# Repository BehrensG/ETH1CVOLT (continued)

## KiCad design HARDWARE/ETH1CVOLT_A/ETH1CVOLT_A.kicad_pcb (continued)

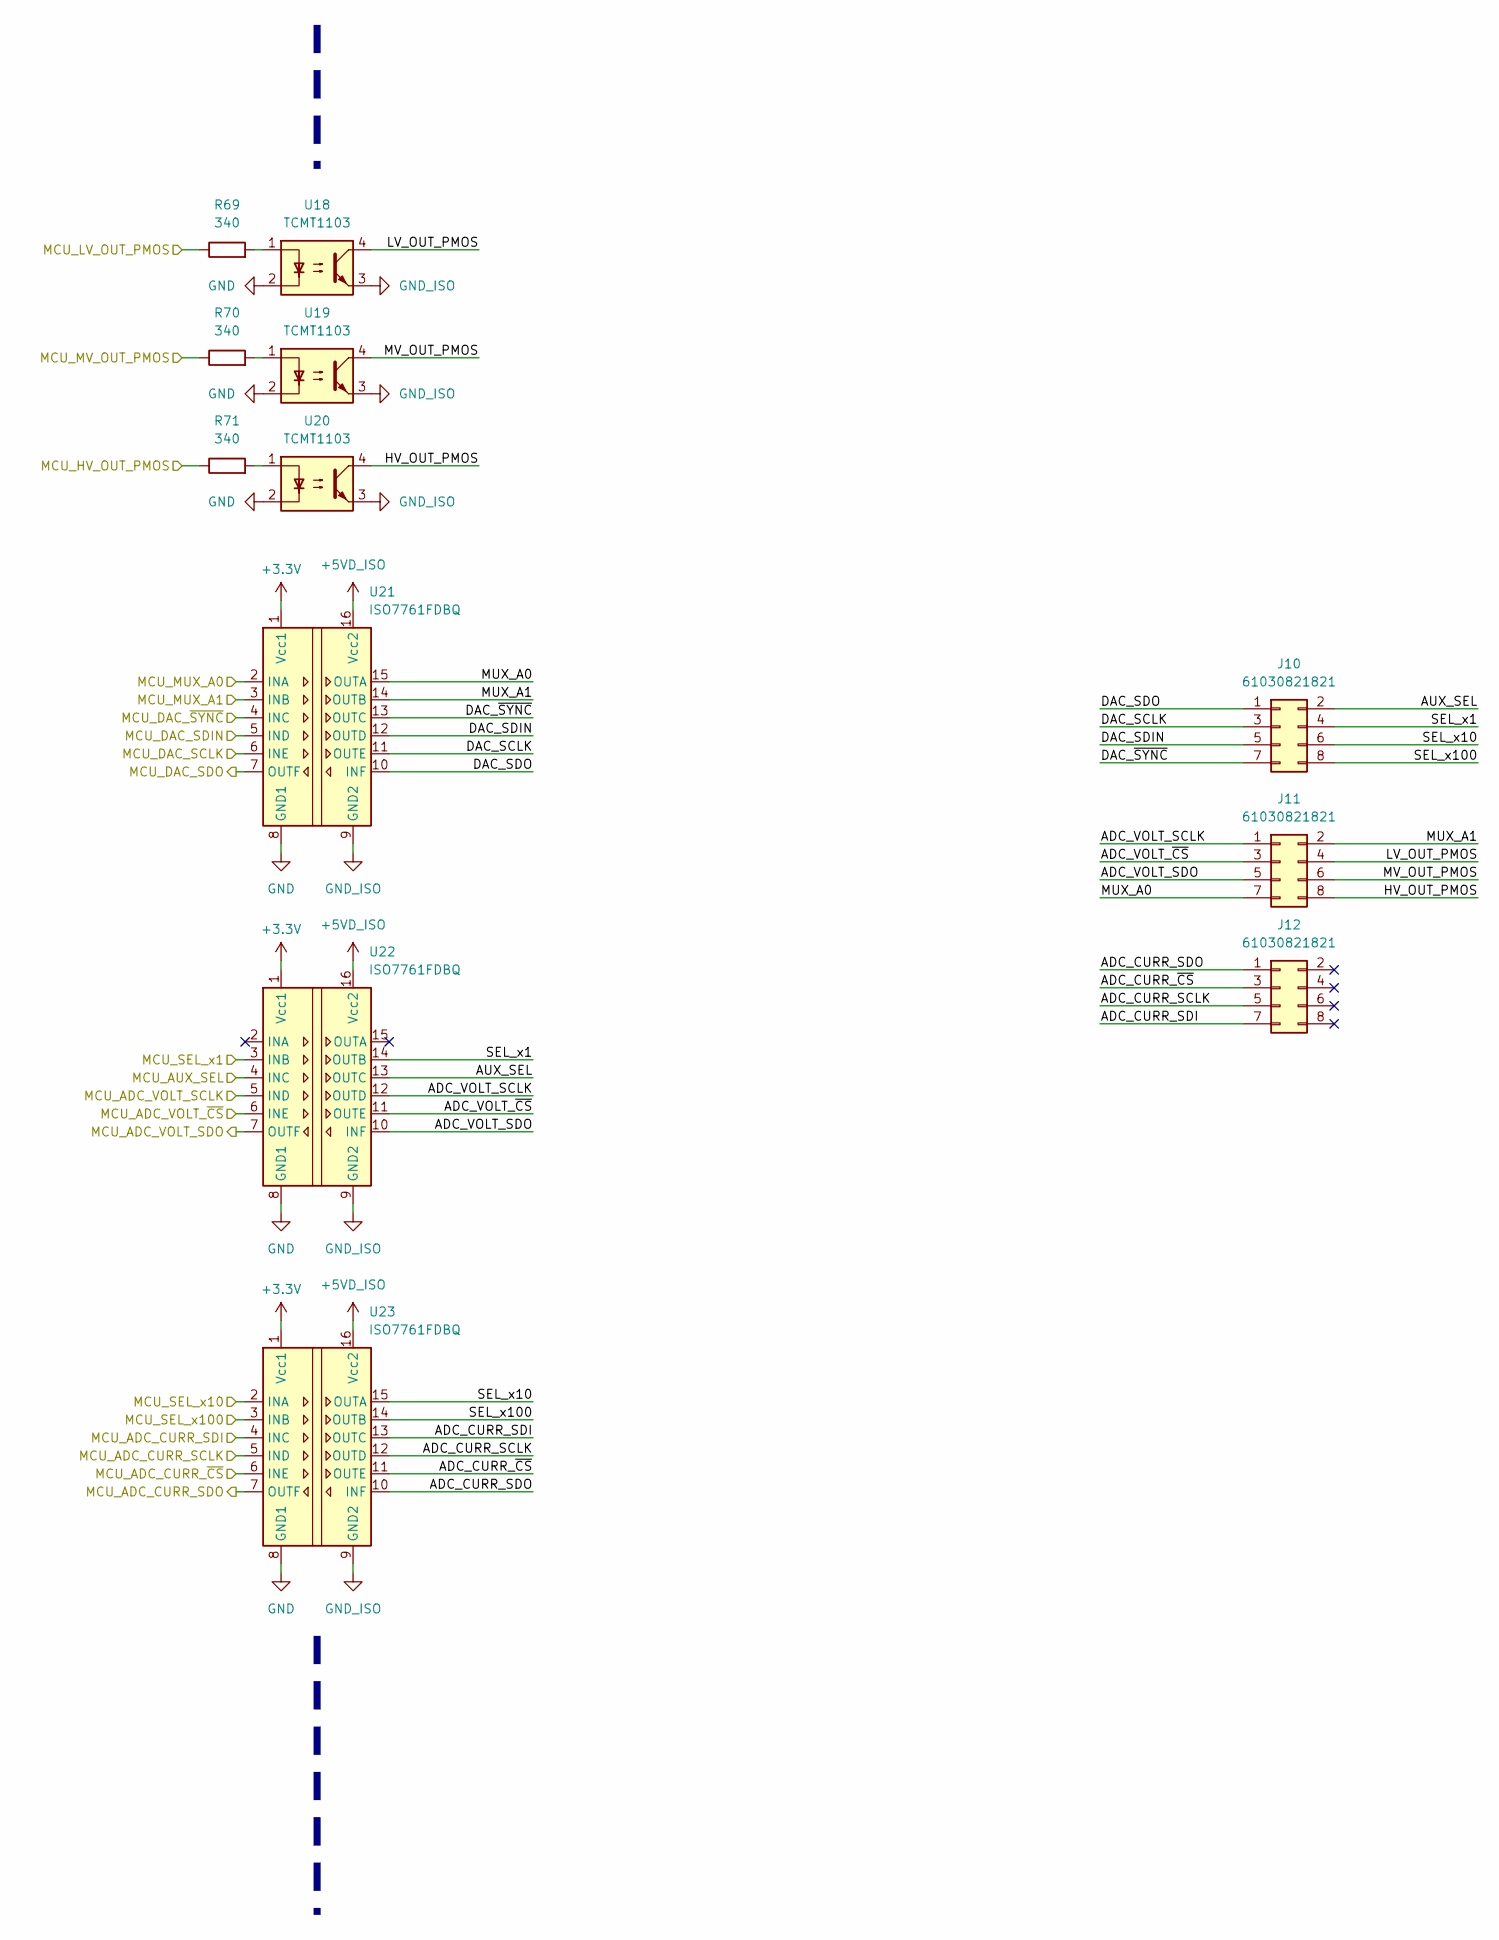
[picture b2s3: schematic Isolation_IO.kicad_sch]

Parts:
J10, J11, J12: 61030821821; PinSocket_2x04_P2.54mm_Vertical_SMD
R69, R70, R71: 340; R_0603_1608Metric_Pad0.98x0.95mm_HandSolder
U18, U19, U20: TCMT1103; SOP-4_4.4x2.6mm_P1.27mm
U21, U22, U23: ISO7761FDBQ; SSOP-16_3.9x4.9mm_P0.635mm

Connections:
+3.3V: U21.1 (Vcc1), U22.1 (Vcc1), U23.1 (Vcc1); also elsewhere on the board
+5VD_ISO: U21.16 (Vcc2), U22.16 (Vcc2), U23.16 (Vcc2); also elsewhere on the board
/Block Diagram/Isolation IO/ADC_CURR_SCLK: J12.5, U23.12 (OUTD)
/Block Diagram/Isolation IO/ADC_CURR_SDI: J12.7, U23.13 (OUTC)
/Block Diagram/Isolation IO/ADC_CURR_SDO: J12.1, U23.10 (INF)
/Block Diagram/Isolation IO/ADC_CURR_~CS: J12.3, U23.11 (OUTE)
/Block Diagram/Isolation IO/ADC_VOLT_SCLK: J11.1, U22.12 (OUTD)
/Block Diagram/Isolation IO/ADC_VOLT_SDO: J11.5, U22.10 (INF)
/Block Diagram/Isolation IO/ADC_VOLT_~CS: J11.3, U22.11 (OUTE)
/Block Diagram/Isolation IO/AUX_SEL: J10.2, U22.13 (OUTC)
/Block Diagram/Isolation IO/DAC_SCLK: J10.3, U21.11 (OUTE)
/Block Diagram/Isolation IO/DAC_SDIN: J10.5, U21.12 (OUTD)
/Block Diagram/Isolation IO/DAC_SDO: J10.1, U21.10 (INF)
/Block Diagram/Isolation IO/DAC_~SYNC: J10.7, U21.13 (OUTC)
/Block Diagram/Isolation IO/HV_OUT_PMOS: J11.8, U20.4
/Block Diagram/Isolation IO/LV_OUT_PMOS: J11.4, U18.4
/Block Diagram/Isolation IO/MCU_ADC_CURR_SCLK: U23.5 (IND); also elsewhere on the board
/Block Diagram/Isolation IO/MCU_ADC_CURR_SDI: U23.4 (INC); also elsewhere on the board
/Block Diagram/Isolation IO/MCU_ADC_CURR_SDO: U23.7 (OUTF); also elsewhere on the board
/Block Diagram/Isolation IO/MCU_ADC_CURR_~CS: U23.6 (INE); also elsewhere on the board
/Block Diagram/Isolation IO/MCU_ADC_VOLT_SCLK: U22.5 (IND); also elsewhere on the board
/Block Diagram/Isolation IO/MCU_ADC_VOLT_SDO: U22.7 (OUTF); also elsewhere on the board
/Block Diagram/Isolation IO/MCU_ADC_VOLT_~CS: U22.6 (INE); also elsewhere on the board
/Block Diagram/Isolation IO/MCU_AUX_SEL: U22.4 (INC); also elsewhere on the board
/Block Diagram/Isolation IO/MCU_DAC_SCLK: U21.6 (INE); also elsewhere on the board
/Block Diagram/Isolation IO/MCU_DAC_SDIN: U21.5 (IND); also elsewhere on the board
/Block Diagram/Isolation IO/MCU_DAC_SDO: U21.7 (OUTF); also elsewhere on the board
/Block Diagram/Isolation IO/MCU_DAC_~SYNC: U21.4 (INC); also elsewhere on the board
/Block Diagram/Isolation IO/MCU_HV_OUT_PMOS: R71.1; also elsewhere on the board
/Block Diagram/Isolation IO/MCU_LV_OUT_PMOS: R69.1; also elsewhere on the board
/Block Diagram/Isolation IO/MCU_MUX_A0: U21.2 (INA); also elsewhere on the board
/Block Diagram/Isolation IO/MCU_MUX_A1: U21.3 (INB); also elsewhere on the board
/Block Diagram/Isolation IO/MCU_MV_OUT_PMOS: R70.1; also elsewhere on the board
/Block Diagram/Isolation IO/MCU_SEL_x1: U22.3 (INB); also elsewhere on the board
/Block Diagram/Isolation IO/MCU_SEL_x10: U23.2 (INA); also elsewhere on the board
/Block Diagram/Isolation IO/MCU_SEL_x100: U23.3 (INB); also elsewhere on the board
/Block Diagram/Isolation IO/MUX_A0: J11.7, U21.15 (OUTA)
/Block Diagram/Isolation IO/MUX_A1: J11.2, U21.14 (OUTB)
/Block Diagram/Isolation IO/MV_OUT_PMOS: J11.6, U19.4
/Block Diagram/Isolation IO/SEL_x1: J10.4, U22.14 (OUTB)
/Block Diagram/Isolation IO/SEL_x10: J10.6, U23.15 (OUTA)
/Block Diagram/Isolation IO/SEL_x100: J10.8, U23.14 (OUTB)
GND: U18.2, U19.2, U20.2, U21.8 (GND1), U22.8 (GND1), U23.8 (GND1); also elsewhere on the board
GND_ISO: U18.3, U19.3, U20.3, U21.9 (GND2), U22.9 (GND2), U23.9 (GND2); also elsewhere on the board
unnamed: R69.2, U18.1
unnamed: R70.2, U19.1
unnamed: R71.2, U20.1

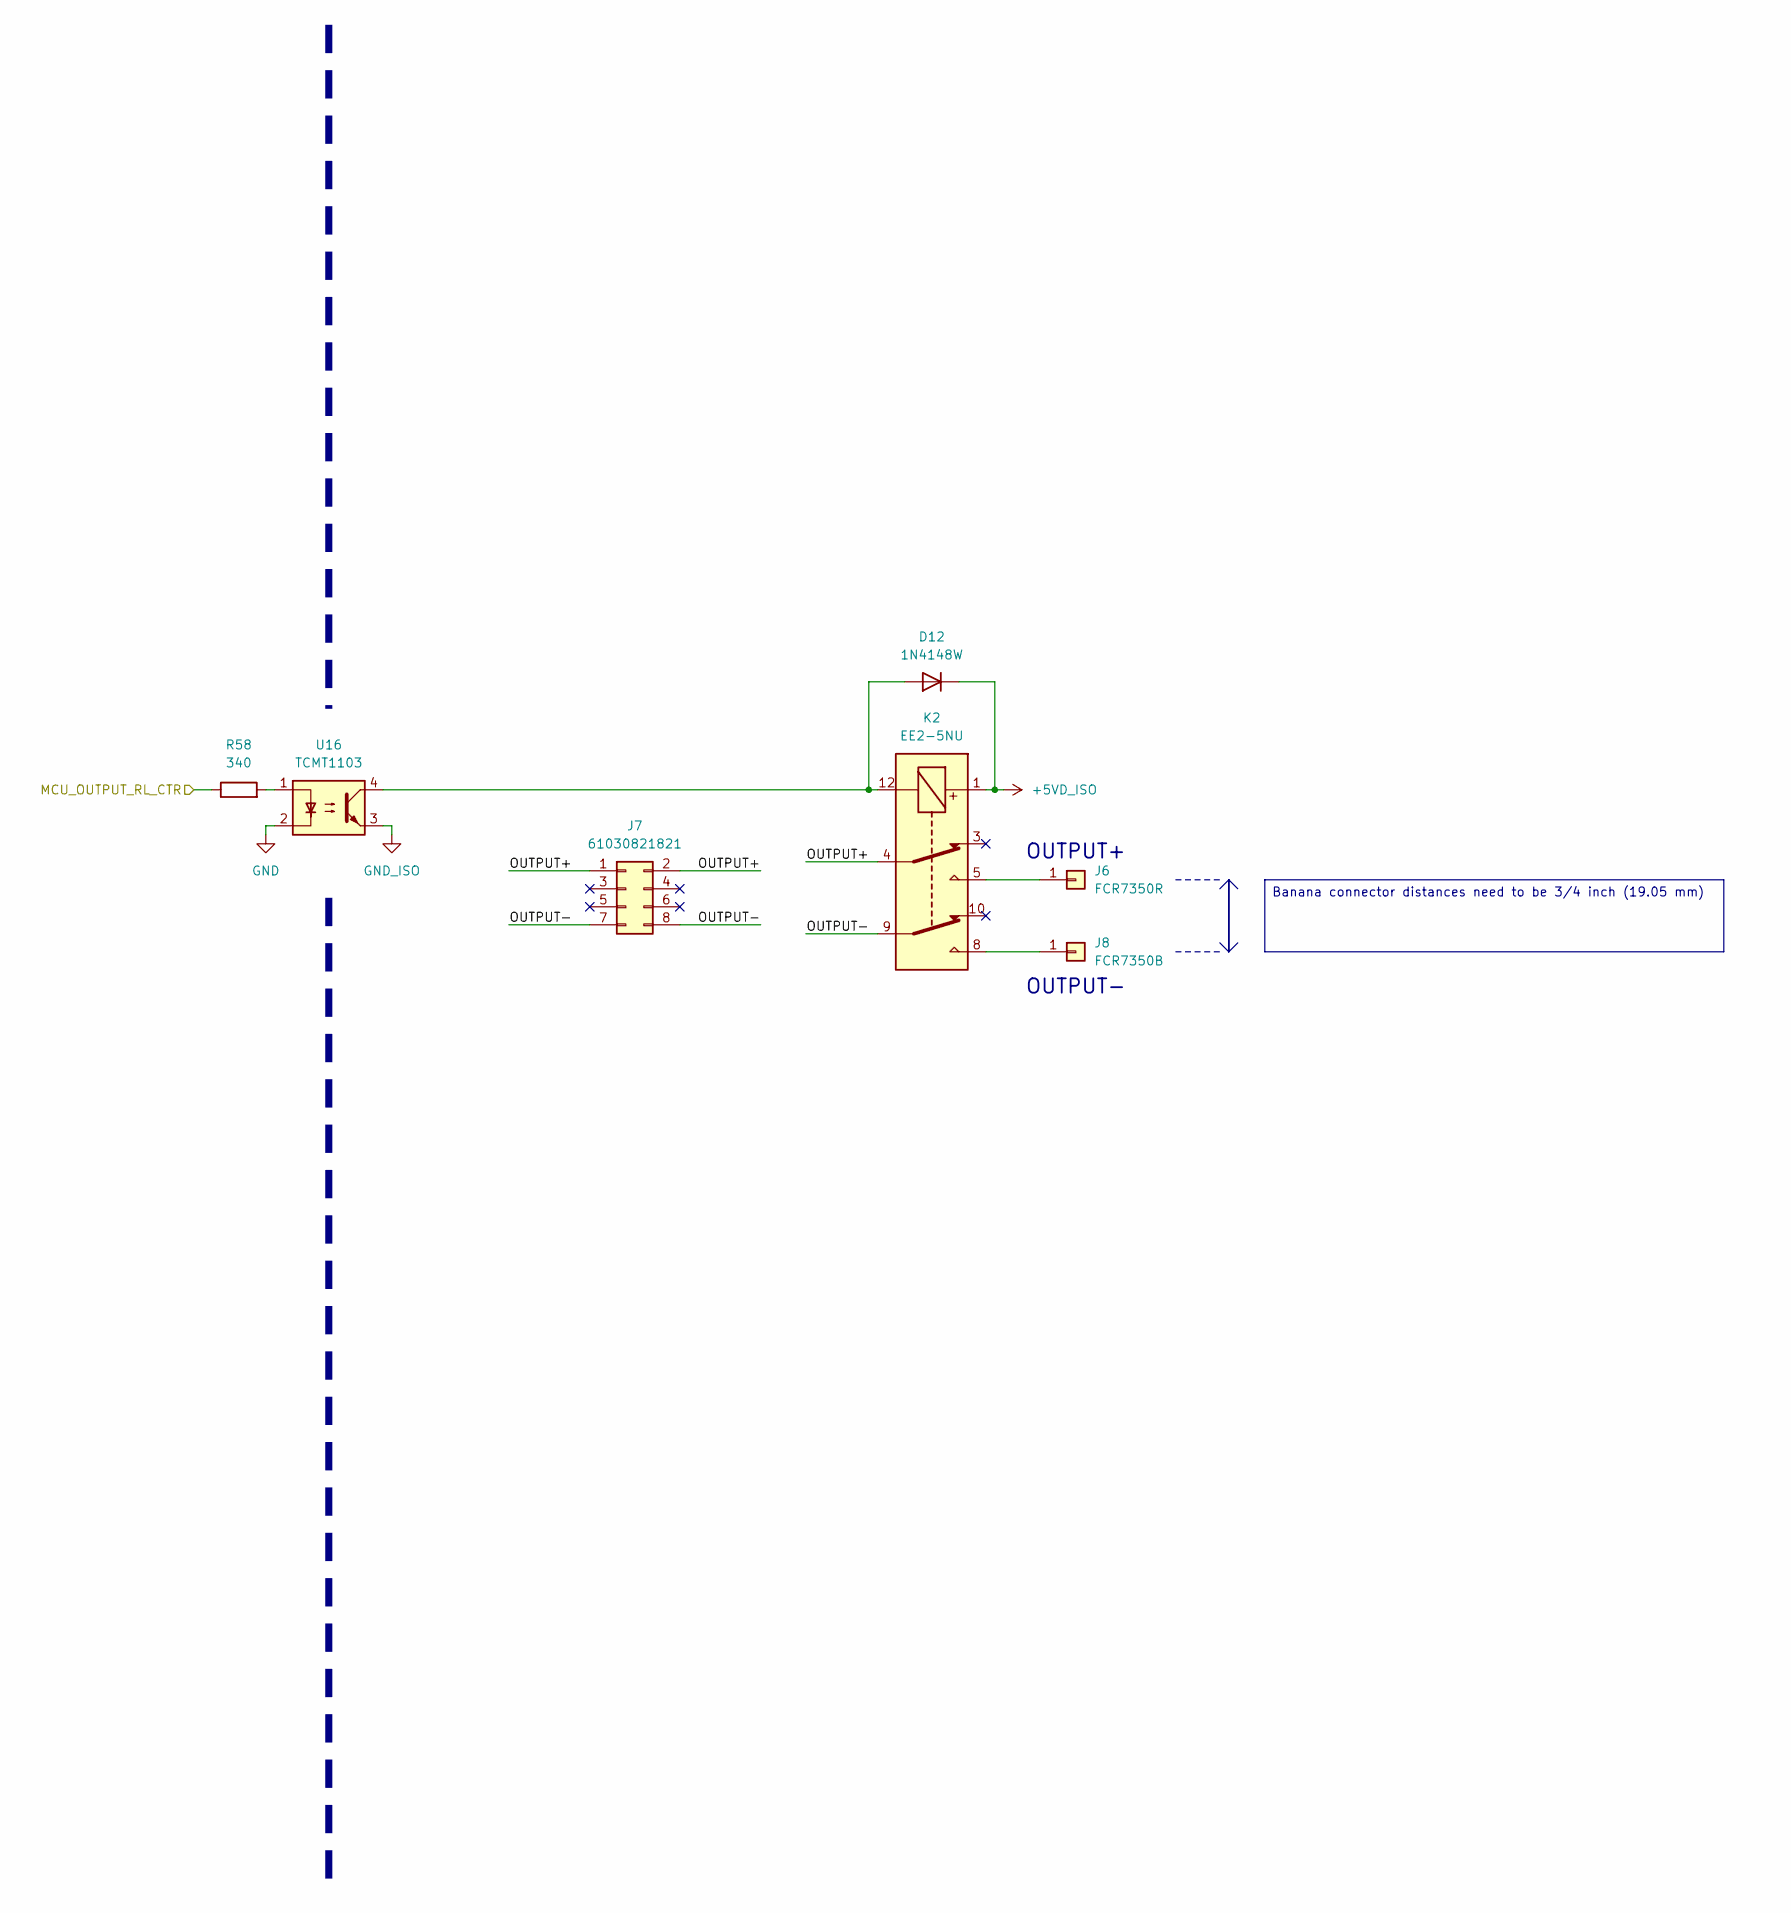
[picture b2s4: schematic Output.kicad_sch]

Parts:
D12: 1N4148W; D_SOD-123
J6: FCR7350R; S16N-PC
J7: 61030821821; PinSocket_2x04_P2.54mm_Vertical_SMD
J8: FCR7350B; S16N-PC
K2: EE2-5NU; Relay_DPDT_Kemet_EE2_NU
R58: 340; R_0603_1608Metric_Pad0.98x0.95mm_HandSolder
U16: TCMT1103; SOP-4_4.4x2.6mm_P1.27mm

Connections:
+5VD_ISO: D12.1 (K), K2.1; also elsewhere on the board
/Block Diagram/MCU/MCU_OUTPUT_RL_CTR: R58.1; also elsewhere on the board
/Block Diagram/Output/OUTPUT+: J7.1, J7.2, K2.4
/Block Diagram/Output/OUTPUT-: J7.7, J7.8, K2.9
GND: U16.2; also elsewhere on the board
GND_ISO: U16.3; also elsewhere on the board
unnamed: D12.2 (A), K2.12, U16.4
unnamed: J6.1 (Pin_1_1), K2.5
unnamed: J8.1 (Pin_1_1), K2.8
unnamed: R58.2, U16.1

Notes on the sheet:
OUTPUT+
OUTPUT-
Banana connector distances need to be 3/4 inch (19.05 mm)

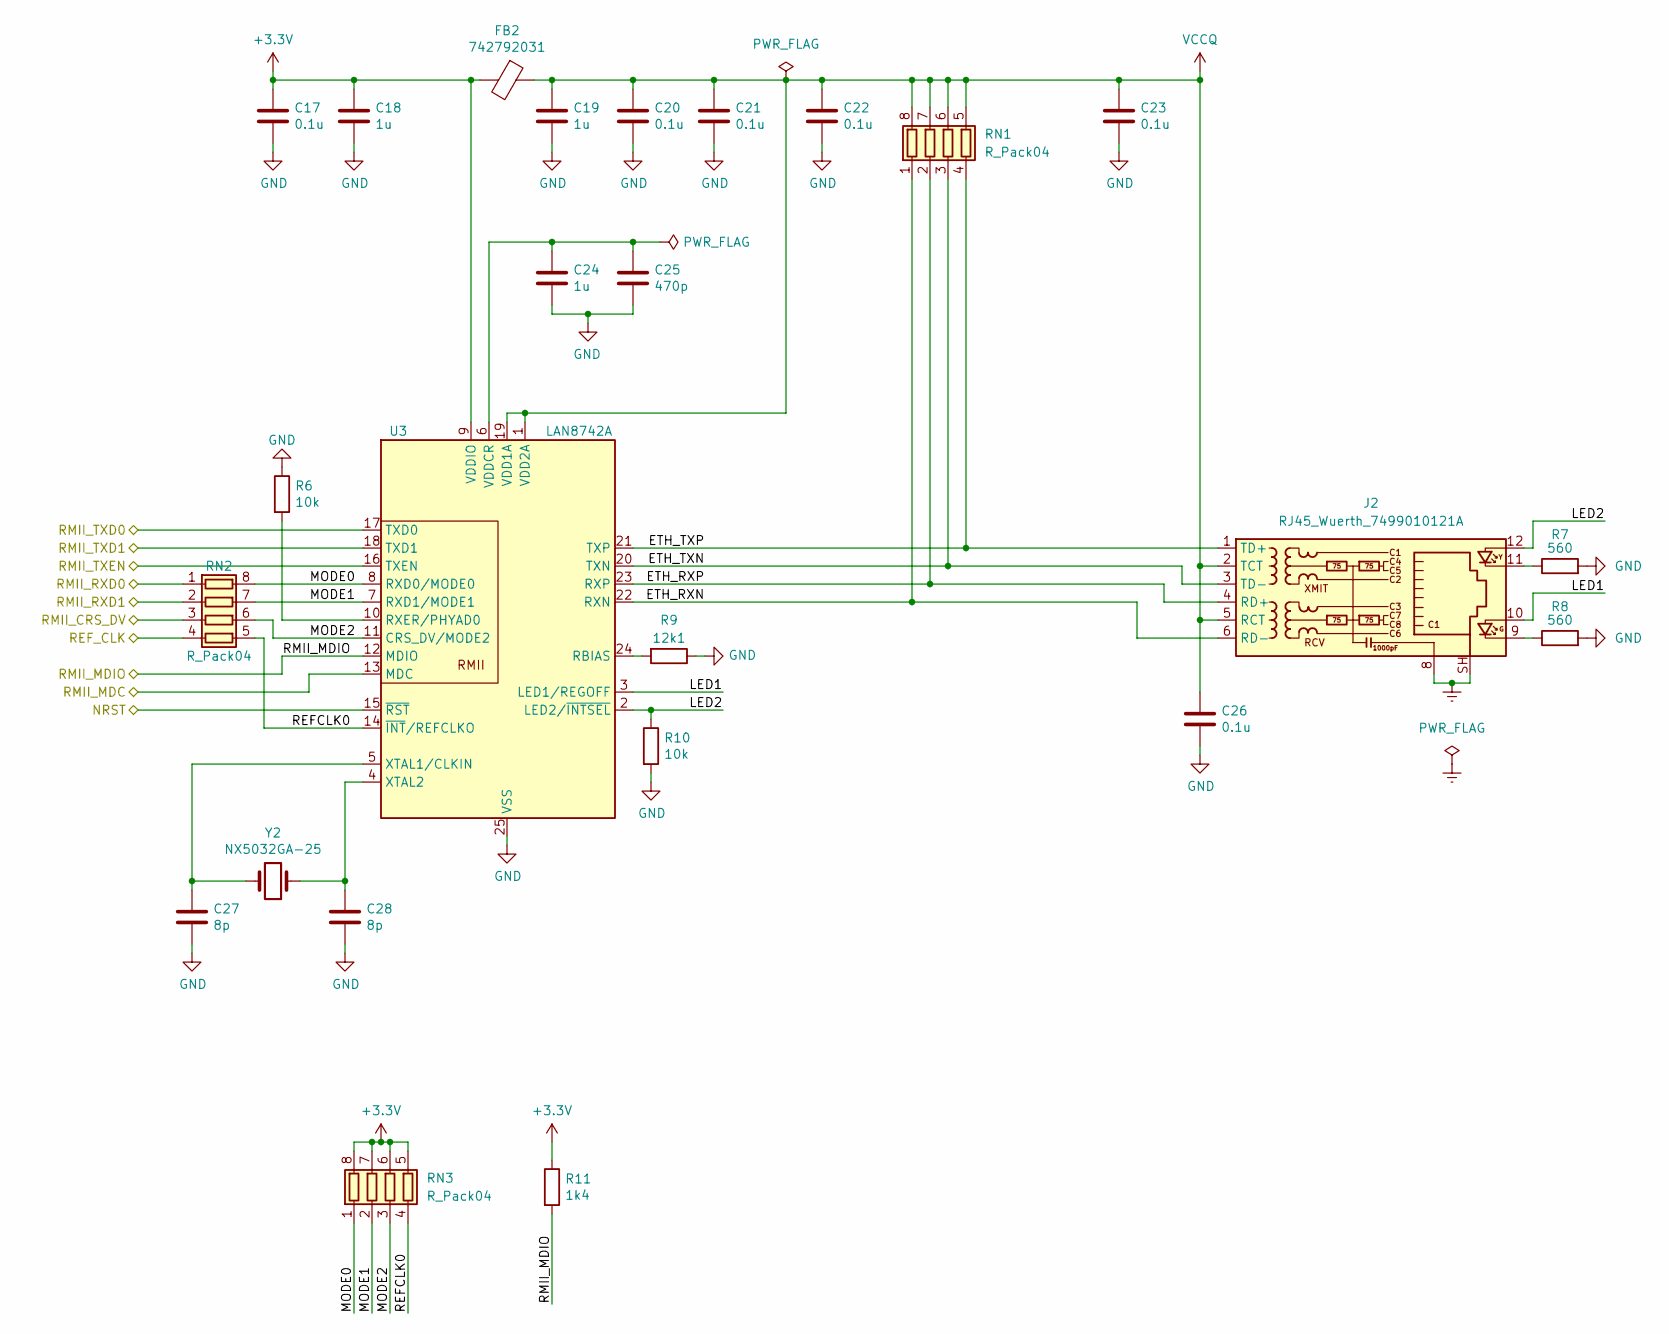
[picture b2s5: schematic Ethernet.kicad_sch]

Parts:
C17, C20, C21, C22, C23, C26: 0.1u; C_0603_1608Metric_Pad1.08x0.95mm_HandSolder
C18, C19, C24: 1u; C_0603_1608Metric_Pad1.08x0.95mm_HandSolder
C25: 470p; C_0603_1608Metric_Pad1.08x0.95mm_HandSolder
C27, C28: 8p; C_0603_1608Metric_Pad1.08x0.95mm_HandSolder
FB2: 742792031; L_0805_2012Metric_Pad1.05x1.20mm_HandSolder
J2: RJ45_Wuerth_7499010121A; RJ45_Wuerth_7499010121A_Horizontal
R6, R10: 10k; R_0603_1608Metric_Pad0.98x0.95mm_HandSolder
R7, R8: 560; R_0603_1608Metric_Pad0.98x0.95mm_HandSolder
R9: 12k1; R_0603_1608Metric_Pad0.98x0.95mm_HandSolder
R11: 1k4; R_0603_1608Metric_Pad0.98x0.95mm_HandSolder
RN1, RN2, RN3: R_Pack04
U3: LAN8742A; VQFN-24-1EP_4x4mm_P0.5mm_EP2.5x2.5mm_ThermalVias
Y2: NX5032GA-25; NX5032GA

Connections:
+3.3V: C17.1, C18.1, FB2.2, R11.1, RN3.5 (R4.2), RN3.6 (R3.2), RN3.7 (R2.2), RN3.8 (R1.2), U3.9 (VDDIO); also elsewhere on the board
/Block Diagram/Ethernet/ETH_RXN: J2.6 (RD-), RN1.1 (R1.1), U3.22 (RXN)
/Block Diagram/Ethernet/ETH_RXP: J2.4 (RD+), RN1.2 (R2.1), U3.23 (RXP)
/Block Diagram/Ethernet/ETH_TXN: J2.3 (TD-), RN1.3 (R3.1), U3.20 (TXN)
/Block Diagram/Ethernet/ETH_TXP: J2.1 (TD+), RN1.4 (R4.1), U3.21 (TXP)
/Block Diagram/Ethernet/LED1: J2.10, U3.3 (LED1/REGOFF)
/Block Diagram/Ethernet/LED2: J2.12, R10.1, U3.2 (LED2/~INTSEL)
/Block Diagram/Ethernet/MODE0: RN2.8 (R1.2), RN3.1 (R1.1), U3.8 (RXD0/MODE0)
/Block Diagram/Ethernet/MODE1: RN2.7 (R2.2), RN3.2 (R2.1), U3.7 (RXD1/MODE1)
/Block Diagram/Ethernet/MODE2: RN2.6 (R3.2), RN3.3 (R3.1), U3.11 (CRS_DV/MODE2)
/Block Diagram/Ethernet/REFCLK0: RN2.5 (R4.2), RN3.4 (R4.1), U3.14 (~INT/REFCLKO)
/Block Diagram/Ethernet/REF_CLK: RN2.4 (R4.1); also elsewhere on the board
/Block Diagram/Ethernet/RMII_CRS_DV: RN2.3 (R3.1); also elsewhere on the board
/Block Diagram/Ethernet/RMII_MDC: U3.13 (MDC); also elsewhere on the board
/Block Diagram/Ethernet/RMII_MDIO: R11.2, U3.12 (MDIO); also elsewhere on the board
/Block Diagram/Ethernet/RMII_RXD0: RN2.1 (R1.1); also elsewhere on the board
/Block Diagram/Ethernet/RMII_RXD1: RN2.2 (R2.1); also elsewhere on the board
/Block Diagram/Ethernet/RMII_TXD0: U3.17 (TXD0); also elsewhere on the board
/Block Diagram/Ethernet/RMII_TXD1: U3.18 (TXD1); also elsewhere on the board
/Block Diagram/Ethernet/RMII_TXEN: U3.16 (TXEN); also elsewhere on the board
/Block Diagram/MCU/NRST: U3.15 (~RST); also elsewhere on the board
Earth: J2.8, J2.SH
GND: C17.2, C18.2, C19.2, C20.2, C21.2, C22.2, C23.2, C24.2, C25.2, C26.2, C27.2, C28.2, R6.1, R7.2, R8.2, R9.1, R10.2, U3.25 (VSS); also elsewhere on the board
unnamed: J2.9, R8.1
unnamed: J2.11, R7.1
unnamed: R9.2, U3.24 (RBIAS)
unnamed: R6.2, U3.10 (RXER/PHYAD0)
unnamed: C24.1, C25.1, U3.6 (VDDCR)
unnamed: C27.1, U3.5 (XTAL1/CLKIN), Y2.2
unnamed: C28.1, U3.4 (XTAL2), Y2.1
VCCQ: C19.1, C20.1, C21.1, C22.1, C23.1, C26.1, FB2.1, J2.2 (TCT), J2.5 (RCT), RN1.5 (R4.2), RN1.6 (R3.2), RN1.7 (R2.2), RN1.8 (R1.2), U3.1 (VDD2A), U3.19 (VDD1A)

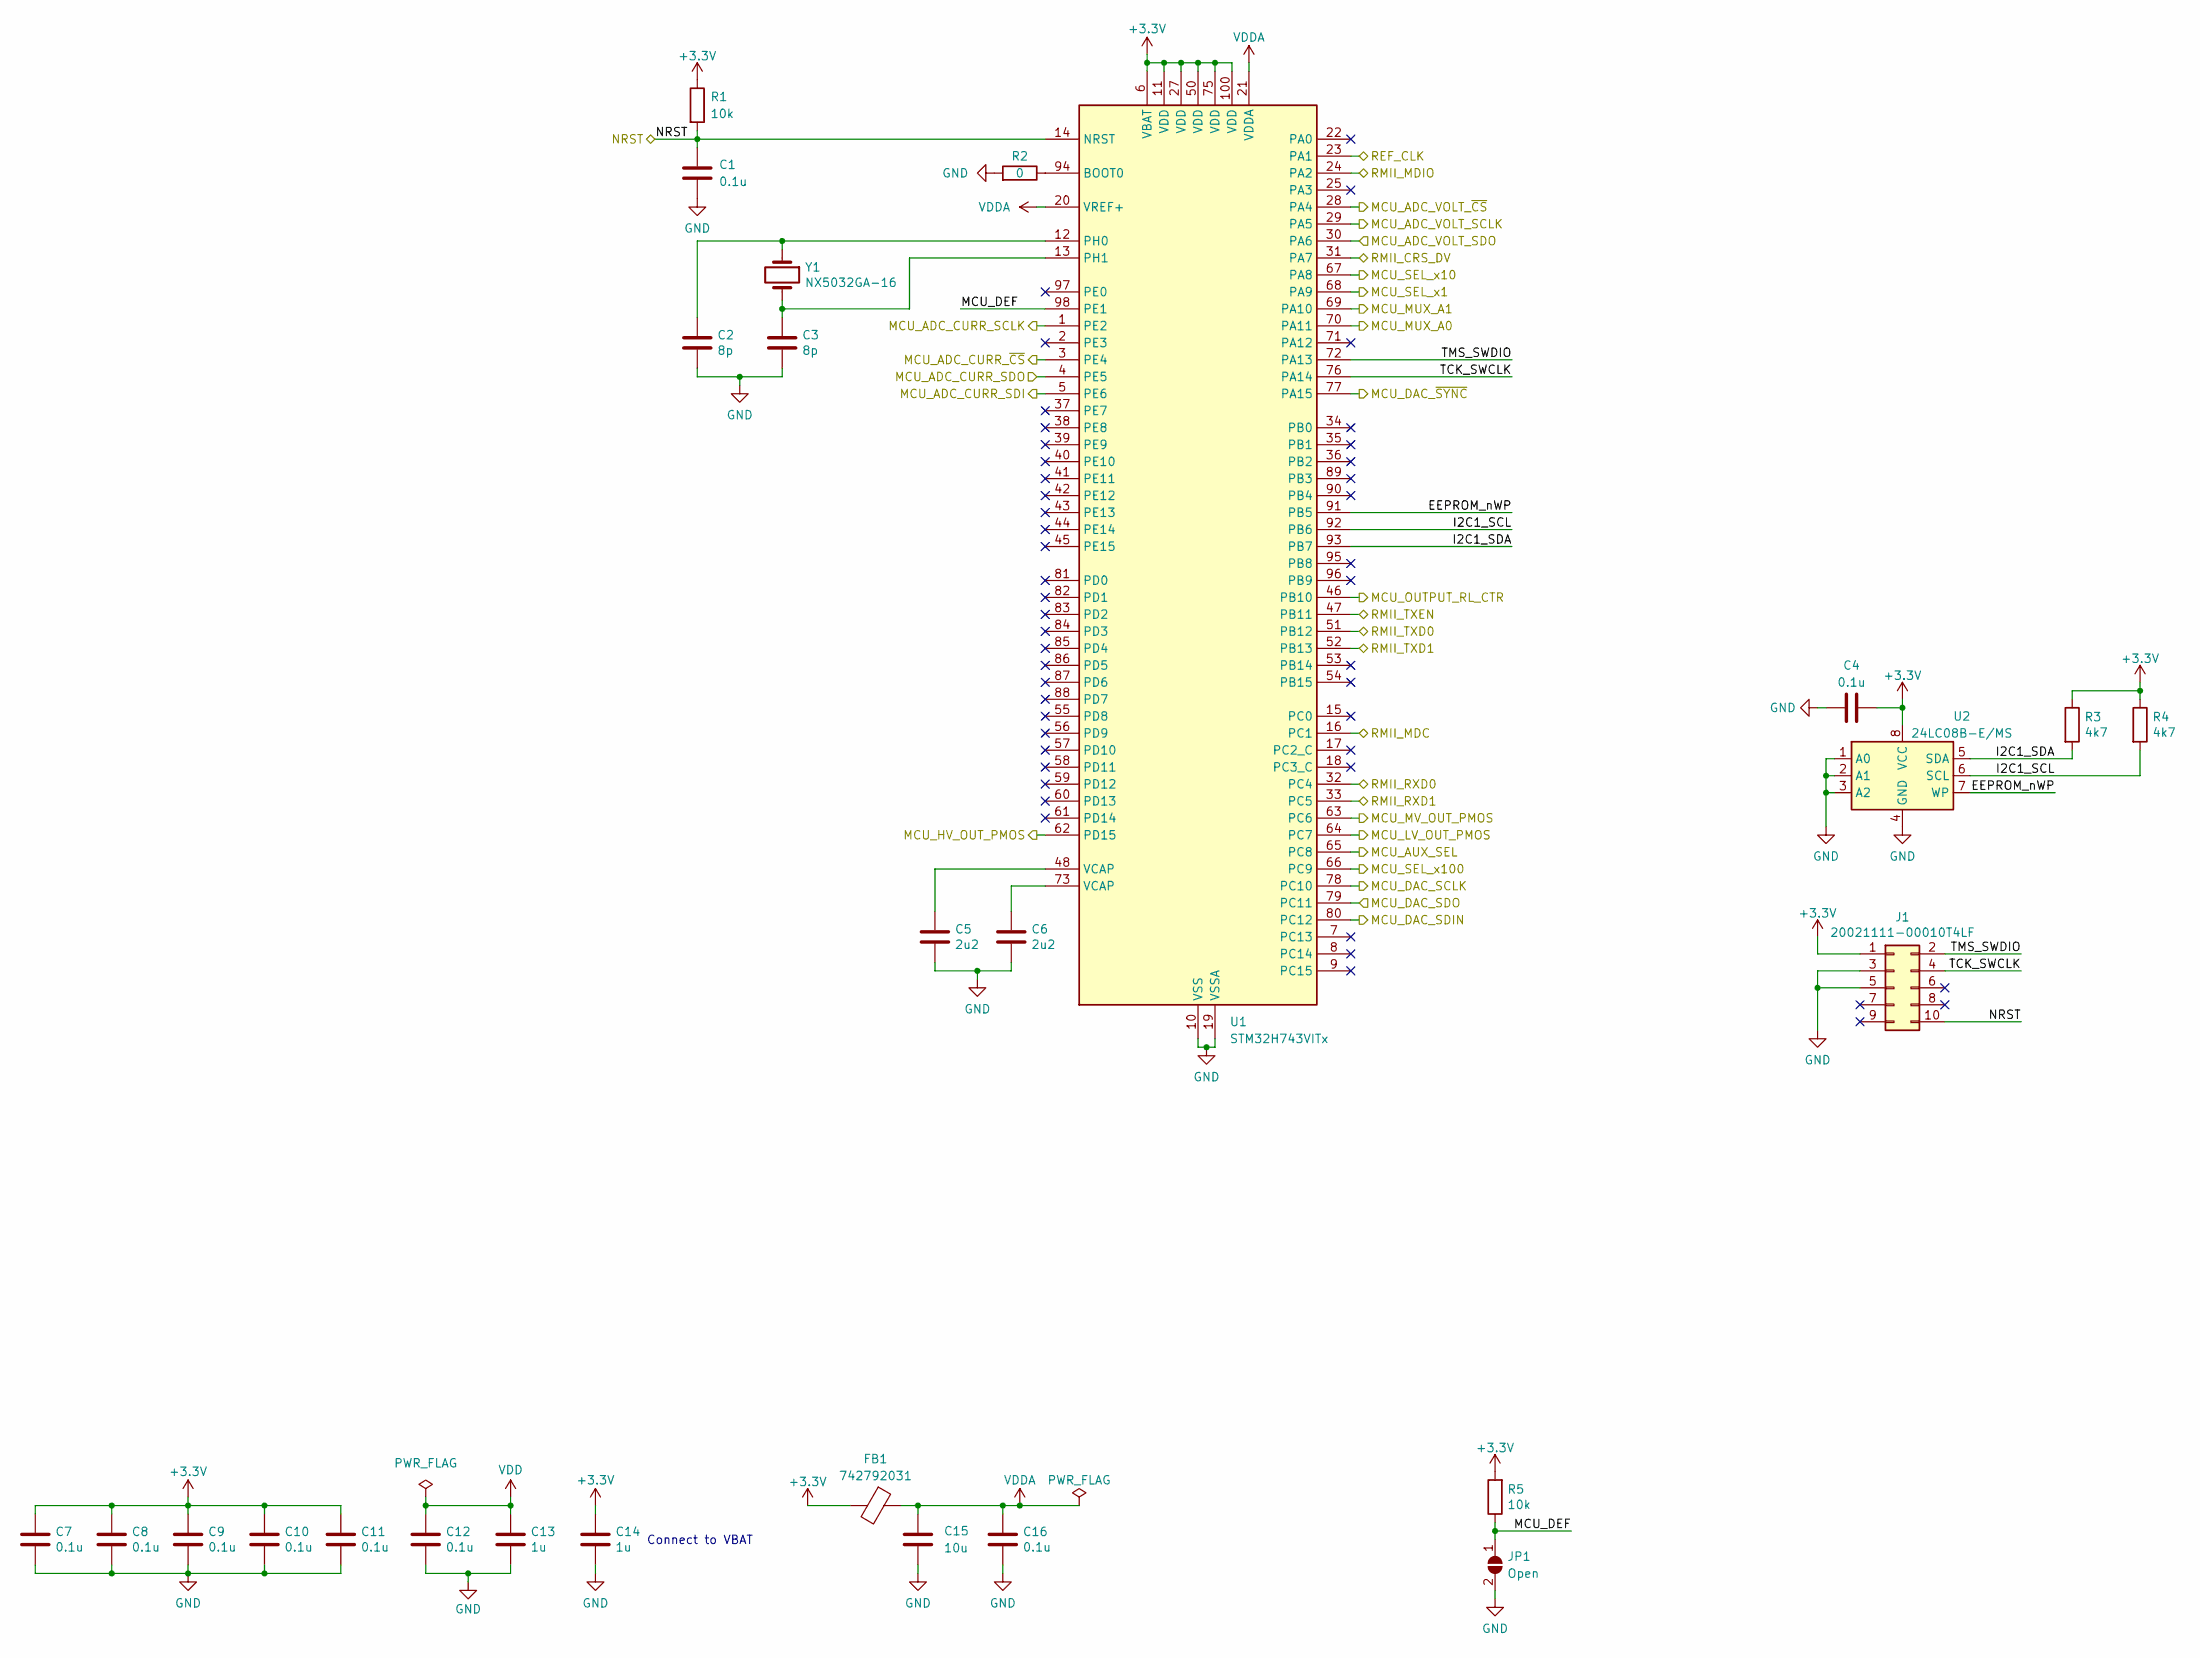
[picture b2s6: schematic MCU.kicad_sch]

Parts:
C1, C4, C7, C8, C9, C10, C11, C12, C16: 0.1u; C_0603_1608Metric_Pad1.08x0.95mm_HandSolder
C2, C3: 8p; C_0603_1608Metric_Pad1.08x0.95mm_HandSolder
C5, C6: 2u2; C_0603_1608Metric_Pad1.08x0.95mm_HandSolder
C13, C14: 1u; C_0603_1608Metric_Pad1.08x0.95mm_HandSolder
C15: 10u; C_0603_1608Metric_Pad1.08x0.95mm_HandSolder
FB1: 742792031; L_0805_2012Metric_Pad1.05x1.20mm_HandSolder
J1: 20021111-00010T4LF; PinHeader_2x05_P1.27mm_Vertical
JP1: Open; SolderJumper-2_P1.3mm_Open_Pad1.0x1.5mm
R1, R5: 10k; R_0603_1608Metric_Pad0.98x0.95mm_HandSolder
R2: 0; R_0603_1608Metric_Pad0.98x0.95mm_HandSolder
R3, R4: 4k7; R_0603_1608Metric_Pad0.98x0.95mm_HandSolder
U1: STM32H743VITx; LQFP-100_14x14mm_P0.5mm
U2: 24LC08B-E/MS; MSOP-8_3x3mm_P0.65mm
Y1: NX5032GA-16; NX5032GA

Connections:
+3.3V: C4.2, C7.1, C8.1, C9.1, C10.1, C11.1, C14.1, FB1.2, J1.1, R1.1, R3.1, R4.1, R5.2, U1.6 (VBAT), U1.11 (VDD), U1.27 (VDD), U1.50 (VDD), U1.75 (VDD), U1.100 (VDD), U2.8 (VCC); also elsewhere on the board
/Block Diagram/Ethernet/REF_CLK: U1.23 (PA1); also elsewhere on the board
/Block Diagram/Ethernet/RMII_CRS_DV: U1.31 (PA7); also elsewhere on the board
/Block Diagram/Ethernet/RMII_MDC: U1.16 (PC1); also elsewhere on the board
/Block Diagram/Ethernet/RMII_MDIO: U1.24 (PA2); also elsewhere on the board
/Block Diagram/Ethernet/RMII_RXD0: U1.32 (PC4); also elsewhere on the board
/Block Diagram/Ethernet/RMII_RXD1: U1.33 (PC5); also elsewhere on the board
/Block Diagram/Ethernet/RMII_TXD0: U1.51 (PB12); also elsewhere on the board
/Block Diagram/Ethernet/RMII_TXD1: U1.52 (PB13); also elsewhere on the board
/Block Diagram/Ethernet/RMII_TXEN: U1.47 (PB11); also elsewhere on the board
/Block Diagram/Isolation IO/MCU_ADC_CURR_SCLK: U1.1 (PE2); also elsewhere on the board
/Block Diagram/Isolation IO/MCU_ADC_CURR_SDI: U1.5 (PE6); also elsewhere on the board
/Block Diagram/Isolation IO/MCU_ADC_CURR_SDO: U1.4 (PE5); also elsewhere on the board
/Block Diagram/Isolation IO/MCU_ADC_CURR_~CS: U1.3 (PE4); also elsewhere on the board
/Block Diagram/Isolation IO/MCU_ADC_VOLT_SCLK: U1.29 (PA5); also elsewhere on the board
/Block Diagram/Isolation IO/MCU_ADC_VOLT_SDO: U1.30 (PA6); also elsewhere on the board
/Block Diagram/Isolation IO/MCU_ADC_VOLT_~CS: U1.28 (PA4); also elsewhere on the board
/Block Diagram/Isolation IO/MCU_AUX_SEL: U1.65 (PC8); also elsewhere on the board
/Block Diagram/Isolation IO/MCU_DAC_SCLK: U1.78 (PC10); also elsewhere on the board
/Block Diagram/Isolation IO/MCU_DAC_SDIN: U1.80 (PC12); also elsewhere on the board
/Block Diagram/Isolation IO/MCU_DAC_SDO: U1.79 (PC11); also elsewhere on the board
/Block Diagram/Isolation IO/MCU_DAC_~SYNC: U1.77 (PA15); also elsewhere on the board
/Block Diagram/Isolation IO/MCU_HV_OUT_PMOS: U1.62 (PD15); also elsewhere on the board
/Block Diagram/Isolation IO/MCU_LV_OUT_PMOS: U1.64 (PC7); also elsewhere on the board
/Block Diagram/Isolation IO/MCU_MUX_A0: U1.70 (PA11); also elsewhere on the board
/Block Diagram/Isolation IO/MCU_MUX_A1: U1.69 (PA10); also elsewhere on the board
/Block Diagram/Isolation IO/MCU_MV_OUT_PMOS: U1.63 (PC6); also elsewhere on the board
/Block Diagram/Isolation IO/MCU_SEL_x1: U1.68 (PA9); also elsewhere on the board
/Block Diagram/Isolation IO/MCU_SEL_x10: U1.67 (PA8); also elsewhere on the board
/Block Diagram/Isolation IO/MCU_SEL_x100: U1.66 (PC9); also elsewhere on the board
/Block Diagram/MCU/EEPROM_nWP: U1.91 (PB5), U2.7 (WP)
/Block Diagram/MCU/I2C1_SCL: R4.2, U1.92 (PB6), U2.6 (SCL)
/Block Diagram/MCU/I2C1_SDA: R3.2, U1.93 (PB7), U2.5 (SDA)
/Block Diagram/MCU/MCU_DEF: JP1.1 (A), R5.1, U1.98 (PE1)
/Block Diagram/MCU/MCU_OUTPUT_RL_CTR: U1.46 (PB10); also elsewhere on the board
/Block Diagram/MCU/NRST: C1.1, J1.10, R1.2, U1.14 (NRST); also elsewhere on the board
/Block Diagram/MCU/TCK_SWCLK: J1.4, U1.76 (PA14)
/Block Diagram/MCU/TMS_SWDIO: J1.2, U1.72 (PA13)
GND: C1.2, C2.2, C3.2, C4.1, C5.2, C6.2, C7.2, C8.2, C9.2, C10.2, C11.2, C12.2, C13.2, C14.2, C15.2, C16.2, J1.3, J1.5, JP1.2 (B), R2.2, U1.10 (VSS), U1.19 (VSSA), U1.26 (VSS), U1.49 (VSS), U1.74 (VSS), U1.99 (VSS), U2.1 (A0), U2.2 (A1), U2.3 (A2), U2.4 (GND); also elsewhere on the board
unnamed: C5.1, U1.48 (VCAP)
unnamed: C6.1, U1.73 (VCAP)
unnamed: R2.1, U1.94 (BOOT0)
unnamed: C2.1, U1.12 (PH0), Y1.1
unnamed: C3.1, U1.13 (PH1), Y1.2
VDD: C12.1, C13.1
VDDA: C15.1, C16.1, FB1.1, U1.20 (VREF+), U1.21 (VDDA)

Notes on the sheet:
Connect to VBAT

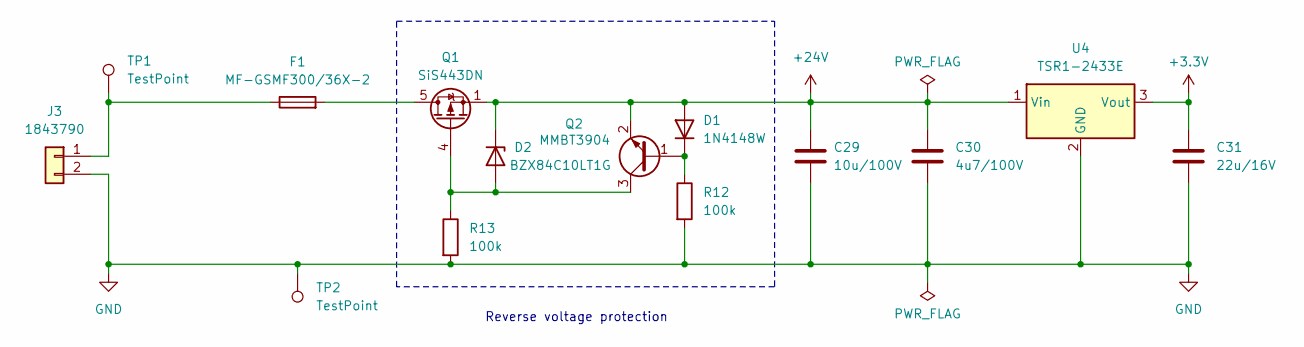
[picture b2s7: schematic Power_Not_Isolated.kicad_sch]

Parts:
C29: 10u/100V; C_1210_3225Metric_Pad1.33x2.70mm_HandSolder
C30: 4u7/100V; C_1210_3225Metric_Pad1.33x2.70mm_HandSolder
C31: 22u/16V; C_1210_3225Metric_Pad1.33x2.70mm_HandSolder
D1: 1N4148W; D_SOD-123
D2: BZX84C10LT1G; SOT-23
F1: MF-GSMF300/36X-2; MF-GSMF
J3: 1843790; PhoenixContact_MC_1,5_2-GF-3.5_1x02_P3.50mm_Horizontal_Thre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
Q1: SiS443DN; Vishay_PowerPAK_1212-8_Single
Q2: MMBT3904; SOT-23
R12, R13: 100k; R_0603_1608Metric_Pad0.98x0.95mm_HandSolder
TP1, TP2: TestPoint; TestPoint_Pad_D2.0mm
U4: TSR1-2433E; Converter_DCDC_TRACO_TSR1-xxxxE_THT

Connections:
+3.3V: C31.1, U4.3 (Vout); also elsewhere on the board
+24V: C29.1, C30.1, D1.2 (A), D2.3 (K), Q1.1 (S), Q1.2 (S), Q1.3 (S), Q2.2 (E), U4.1 (Vin); also elsewhere on the board
GND: C29.2, C30.2, C31.2, J3.2, R12.2, R13.2, TP2.1 (1_1), U4.2 (GND); also elsewhere on the board
unnamed: D1.1 (K), Q2.1 (B), R12.1
unnamed: D2.1 (A), Q1.4 (G), Q2.3 (C), R13.1
unnamed: F1.1, J3.1, TP1.1 (1_1)
unnamed: F1.2, Q1.5 (D)

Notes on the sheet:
Reverse voltage protection
